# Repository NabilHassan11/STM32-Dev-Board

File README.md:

# STM32-Dev-Board
# STM32F103C8T6 Development Board

## Overview
This is a custom **STM32F103C8T6 development board** designed for embedded systems and firmware development. It provides an easy-to-use platform for programming, debugging, and prototyping STM32-based projects.

## Features
✅ **Microcontroller:** STM32F103C8T6 (ARM Cortex-M3, 72MHz, 64KB Flash, 20KB RAM)  
✅ **Power Input:** USB-B Micro for power and data transfer  
✅ **Programming & Debugging:** SWD header for easy debugging with ST-Link  
✅ **Reset & Boot Buttons:** Tactile push buttons for **RESET** and **BOOT mode selection**  
✅ **Connectivity:**  
   - **USART header & I2C ** for serial communication  
   - **Multiple GPIO breakout pins** for external peripherals  
✅ **Power Regulation:** Onboard **LDO voltage regulator** for stable 3.3V operation  
✅ **Crystal Oscillator:** 16MHz main clock 

## Applications
- Embedded systems development
- IoT prototyping
- Motor control & robotics
- Educational & hobby projects

## Repository Contents
📁 **Hardware:** KiCad design files, schematics, and PCB layout
📁 **Documentation:** BOM, assembly guide, and pinout diagrams  

---
### Author
**Nabil Hassan**

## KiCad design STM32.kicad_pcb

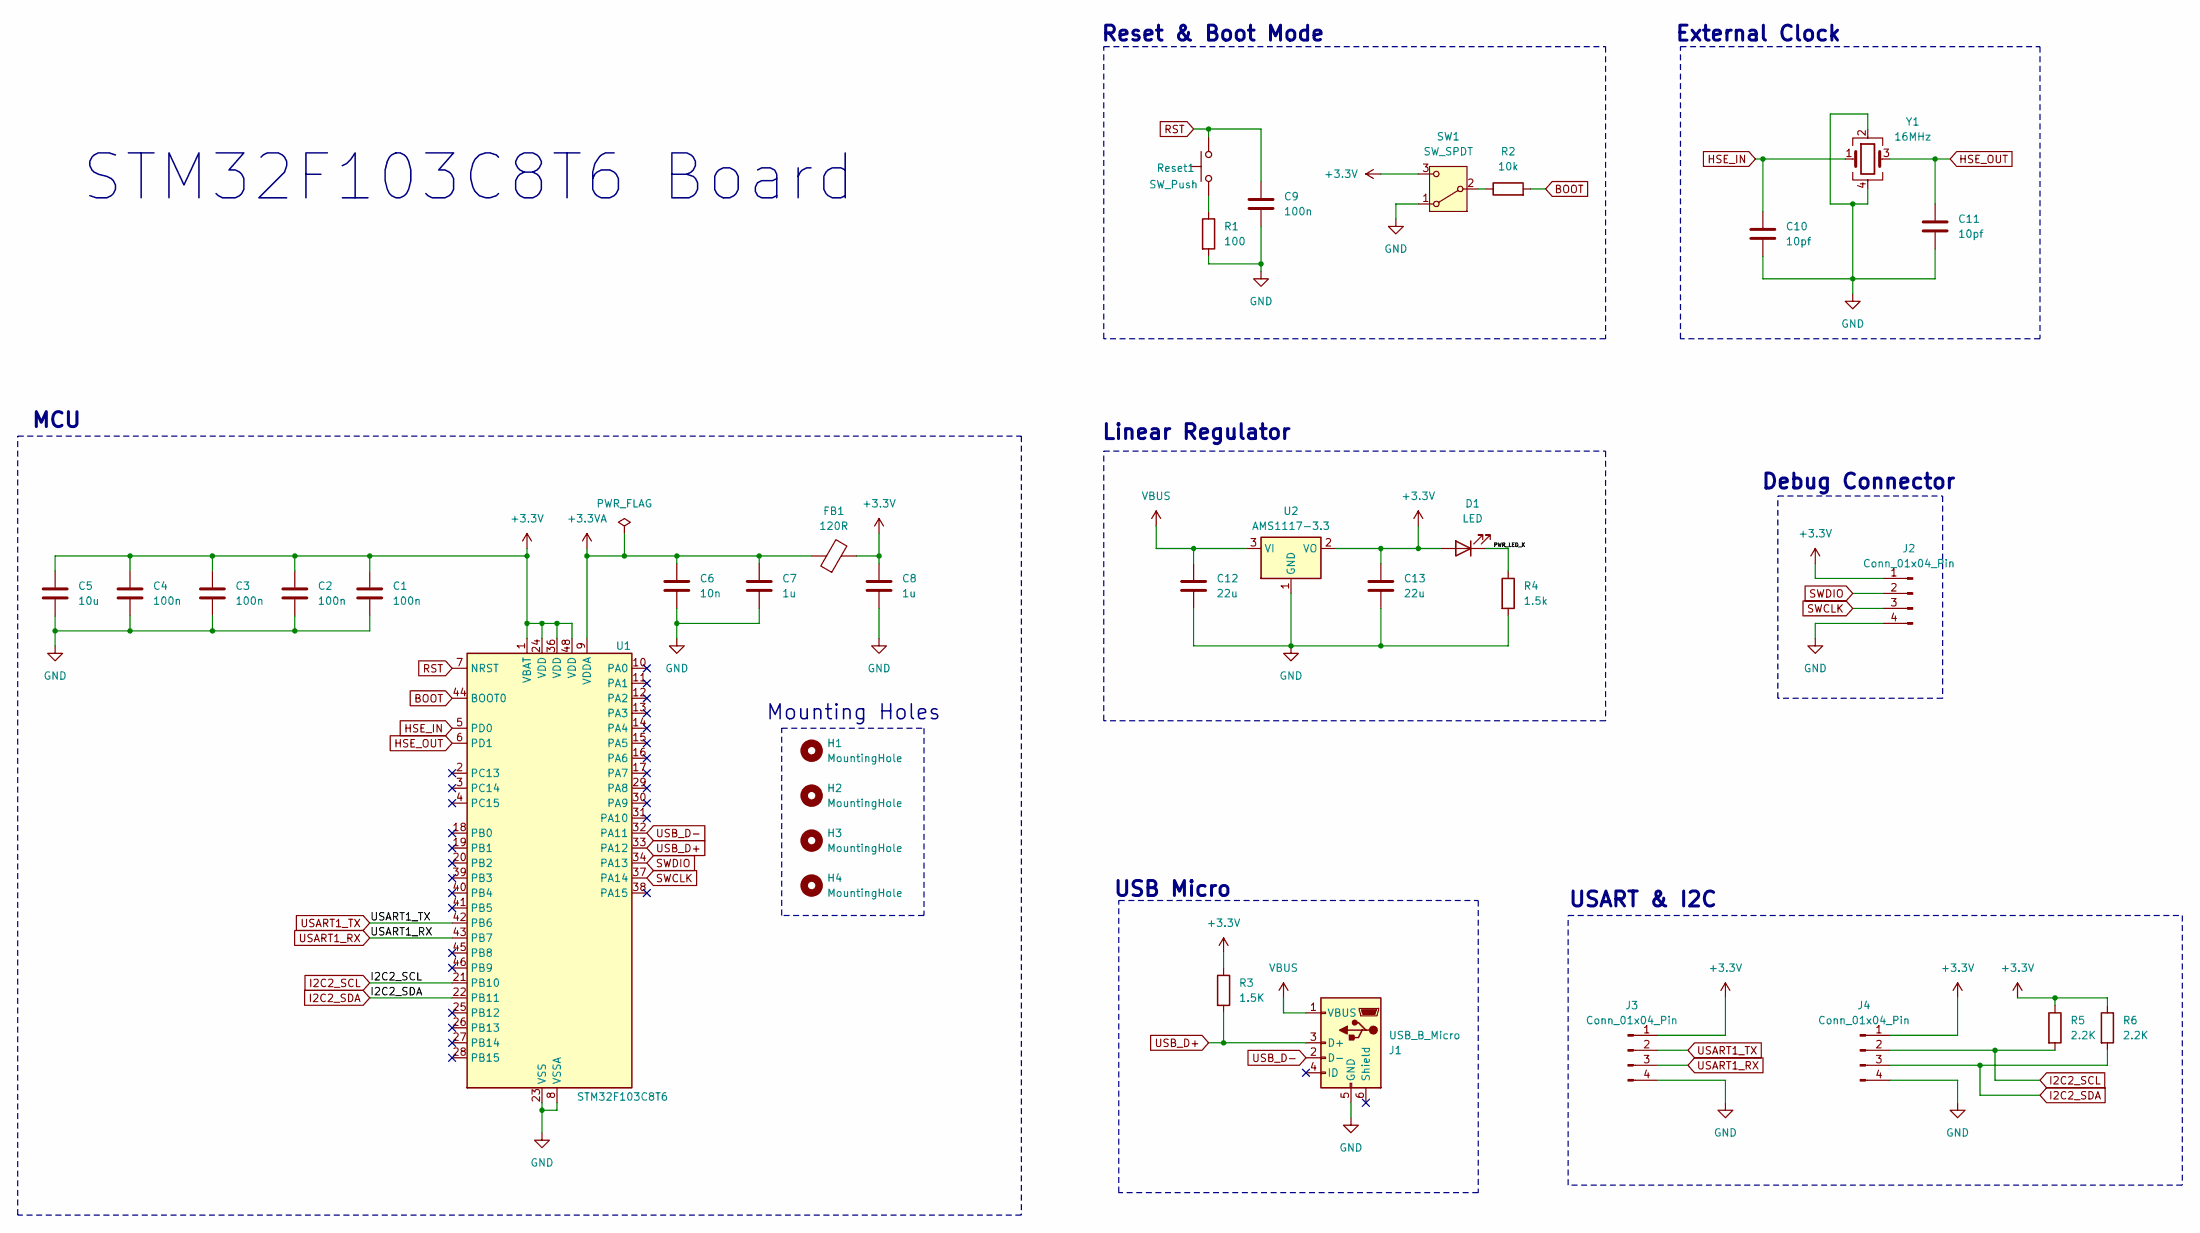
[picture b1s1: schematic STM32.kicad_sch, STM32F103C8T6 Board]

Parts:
C1, C2, C3, C4, C9: 100n; C_0402_1005Metric
C5: 10u; C_0603_1608Metric
C6: 10n; C_0402_1005Metric
C7, C8: 1u; C_0402_1005Metric
C10, C11: 10pf; C_0402_1005Metric
C12, C13: 22u; C_0805_2012Metric
D1: LED; LED_0603_1608Metric
FB1: 120R; L_0603_1608Metric
H1, H2, H3, H4: MountingHole; MountingHole_2.2mm_M2
J1: USB_B_Micro; USB_Micro-B_Wuerth_629105150521
J2, J3, J4: Conn_01x04_Pin; PinHeader_1x04_P2.54mm_Vertical
R1: 100; R_0402_1005Metric
R2: 10k; R_0402_1005Metric
R3: 1.5K; R_0402_1005Metric
R4: 1.5k; R_0402_1005Metric
R5, R6: 2.2K; R_0402_1005Metric
Reset1: SW_Push; SW_PUSH_6mm
SW1: SW_SPDT; SW_SPDT_PCM12
U1: STM32F103C8T6; LQFP-48_7x7mm_P0.5mm
U2: AMS1117-3.3; SOT-223-3_TabPin2
Y1: 16MHz; Crystal_SMD_3225-4Pin_3.2x2.5mm

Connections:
+3.3V: C1.1, C2.1, C3.1, C4.1, C5.1, C8.1, C13.1, D1.2 (A), FB1.2, J2.1, J3.1, J4.1, R3.1, R5.1, R6.1, SW1.3 (C), U1.1 (VBAT), U1.24 (VDD), U1.36 (VDD), U1.48 (VDD), U2.2 (VO); also elsewhere on the board
+3.3VA: C6.1, C7.1, FB1.1, U1.9 (VDDA)
/PWR_LED_K: D1.1 (K), R4.1
BOOT: R2.2, U1.44 (BOOT0)
GND: C1.2, C2.2, C3.2, C4.2, C5.2, C6.2, C7.2, C8.2, C9.2, C10.2, C11.2, C12.2, C13.2, J1.5 (GND), J2.4, J3.4, J4.4, R1.2, R4.2, SW1.1 (A), U1.8 (VSSA), U1.23 (VSS), U1.35 (VSS), U1.47 (VSS), U2.1 (GND), Y1.2, Y1.4; also elsewhere on the board
HSE_IN: C10.1, U1.5 (PD0), Y1.1
HSE_OUT: C11.1, U1.6 (PD1), Y1.3
I2C2_SCL: J4.2, R5.2, U1.21 (PB10); also elsewhere on the board
I2C2_SDA: J4.3, R6.2, U1.22 (PB11); also elsewhere on the board
unnamed 9: R1.1, Reset1.1; also elsewhere on the board
unnamed: R2.1, SW1.2 (B)
RST: C9.1, Reset1.2, U1.7 (NRST); also elsewhere on the board
SWCLK: J2.3, U1.37 (PA14)
SWDIO: J2.2, U1.34 (PA13)
USART1_RX: J3.3, U1.43 (PB7); also elsewhere on the board
USART1_TX: J3.2, U1.42 (PB6); also elsewhere on the board
USB_D+: J1.3 (D+), R3.2, U1.33 (PA12)
USB_D-: J1.2 (D-), U1.32 (PA11)
VBUS: C12.1, J1.1 (VBUS), U2.3 (VI)

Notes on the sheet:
STM32F103C8T6 Board
Linear Regulator
USART & I2C
Reset & Boot Mode
External Clock
MCU
USB Micro
Mounting Holes
Debug Connector

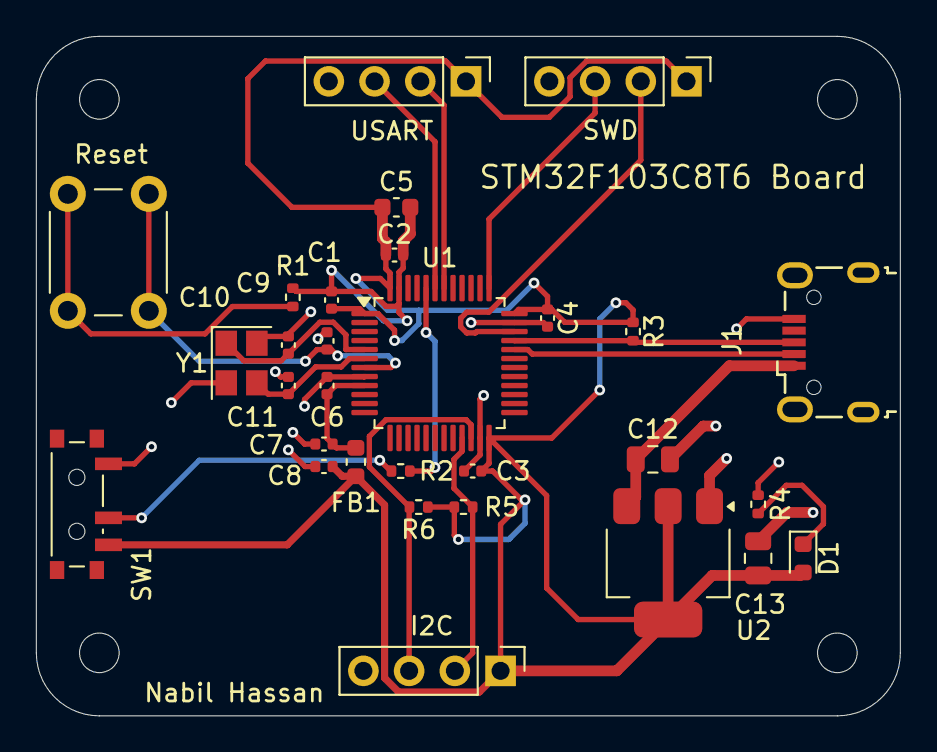
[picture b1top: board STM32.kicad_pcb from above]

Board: 2 copper layers, 48.0 x 37.8 mm, 34 parts (0 on the bottom side), 19 nets.

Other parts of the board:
I2C: Conn_01x04_Pin; PinHeader_1x04_P2.54mm_Vertical
Reset: SW_Push; SW_PUSH_6mm
USART: Conn_01x04_Pin; PinHeader_1x04_P2.54mm_Vertical

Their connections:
+3.3V: I2C.1, USART.1; also elsewhere on the board
GND: I2C.4, USART.4; also elsewhere on the board
I2C2_SCL: I2C.2; also elsewhere on the board
I2C2_SDA: I2C.3; also elsewhere on the board
unnamed 9: Reset.1; also elsewhere on the board
RST: Reset.2; also elsewhere on the board
USART1_RX: USART.3; also elsewhere on the board
USART1_TX: USART.2; also elsewhere on the board

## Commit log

2025-05-01 Create LICENSE
